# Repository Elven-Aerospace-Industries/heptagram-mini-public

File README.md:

# Heptagram Mini
Open-source simple flight control computer solution

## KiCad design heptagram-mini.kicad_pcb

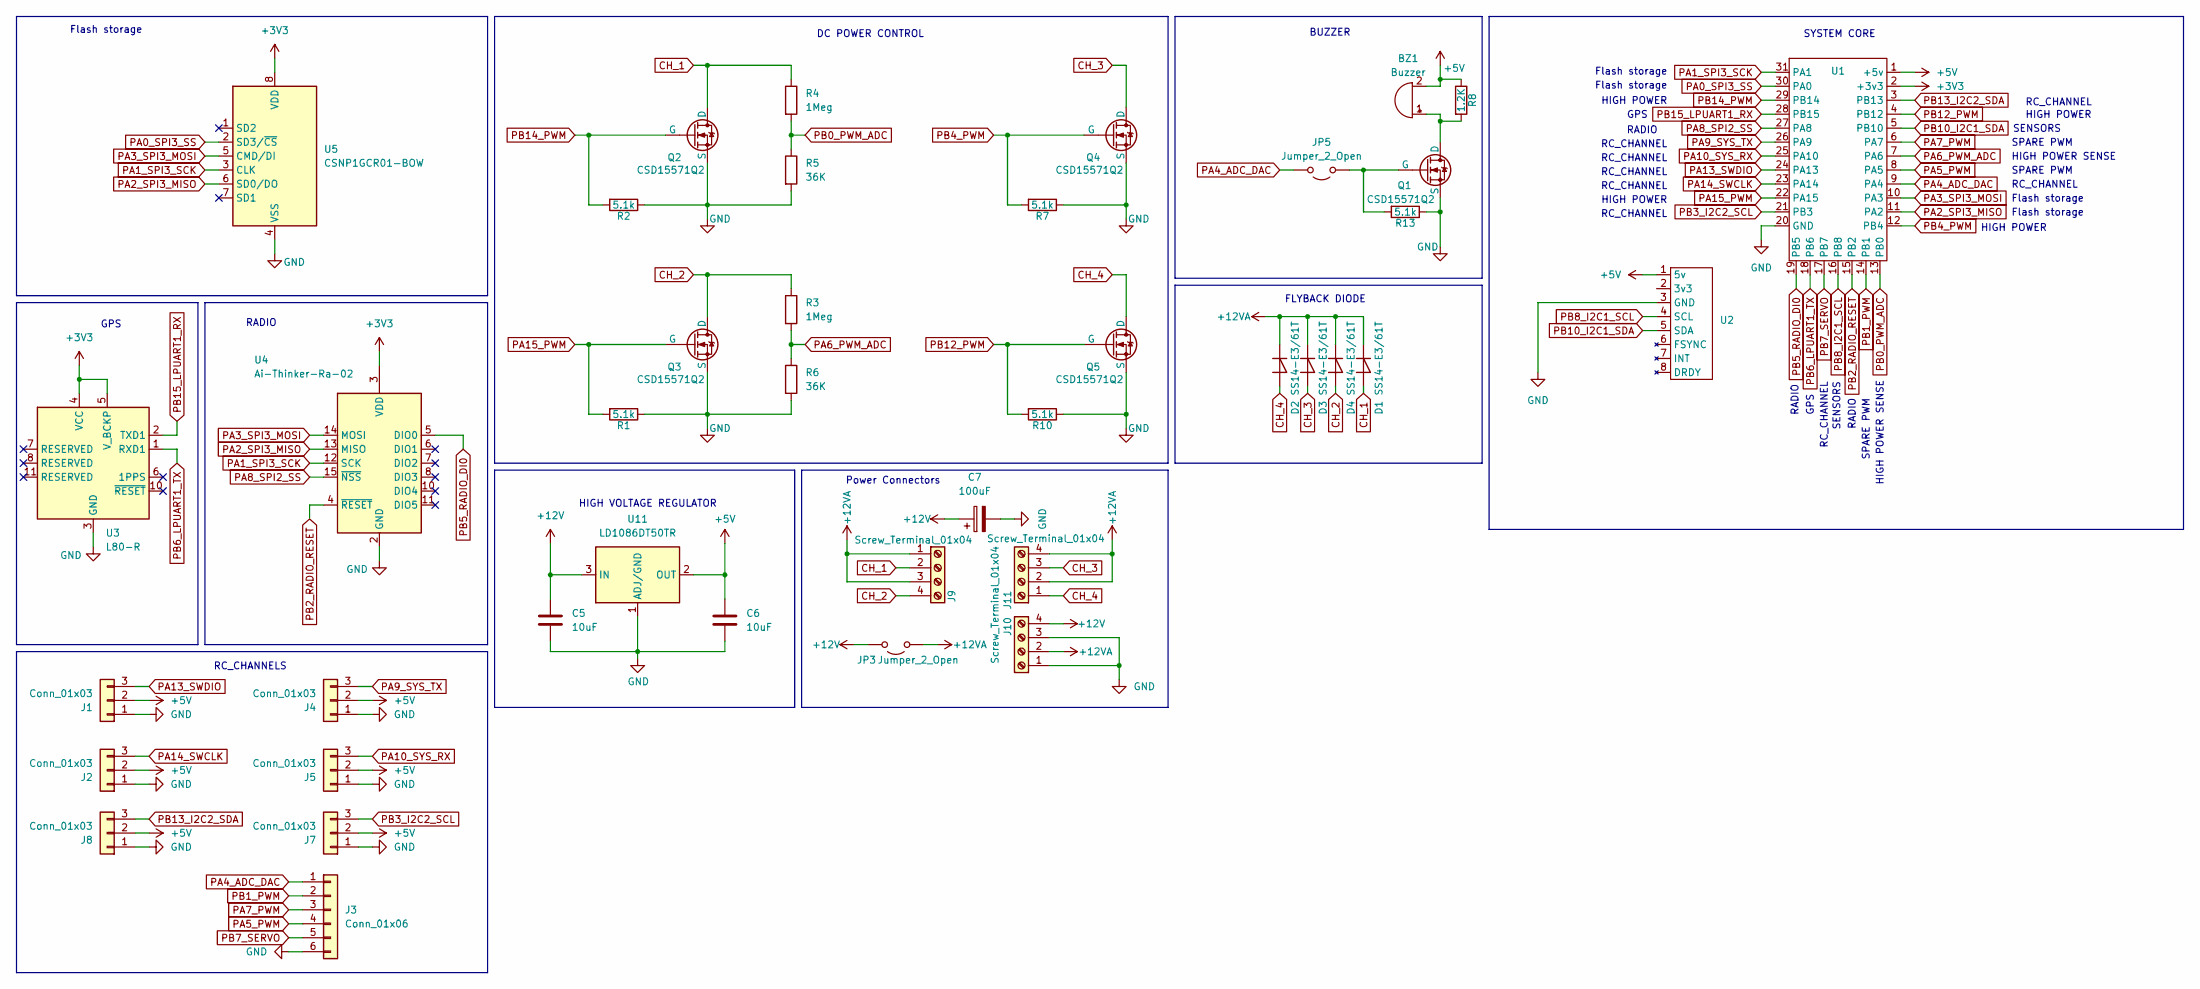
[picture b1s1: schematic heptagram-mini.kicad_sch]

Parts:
BZ1: Buzzer; Buzzer_hand_solder; LCSC C201042
C5, C6: 10uF; C_0402_1005Metric; LCSC C15525
C7: 100uF; CP_EIA-7343-30_AVX-N; LCSC C7223
D1, D2, D3, D4: SS14-E3/61T; D_SMA; LCSC C47460
J1, J2, J4, J5, J7, J8: Conn_01x03; 3pin
J3: Conn_01x06; PinHeader_1x06_P2.54mm_Vertical
J9, J10, J11: Screw_Terminal_01x04; TerminalBlock_Xinya_XY308-2.54-4P_1x04_P2.54mm_Horizontal
JP3, JP5: Jumper_2_Open; SolderJumper-2_P1.3mm_Open_RoundedPad1.0x1.5mm
Q1, Q2, Q3, Q4, Q5: CSD15571Q2; flight_computer_Texas_DQK; LCSC C412825
R1, R2, R7, R10, R13: 5.1k; R_0402_1005Metric_Pad0.72x0.64mm_HandSolder; LCSC C25905
R3, R4: 1Meg; R_0805_2012Metric; LCSC C17514
R5, R6: 36K; R_0805_2012Metric; LCSC C4360
R8: 1.2K; R_0603_1608Metric_Pad0.98x0.95mm_HandSolder; LCSC C22765
U1: laplace0_lite
U2: GY87
U3: L80-R; Quectel_L80-R; LCSC C3029061
U4: Ai-Thinker-Ra-02; Ai-Thinker-Ra-01-LoRa
U5: CSNP1GCR01-BOW; LGA-8_8x6mm_P1.27mm; LCSC C2691593
U11: LD1086DT50TR; TO-252-2; LCSC C164853

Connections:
+3V3: U1.2 (+3v3), U3.4 (VCC), U3.5 (V_BCKP), U4.3 (VDD), U5.8 (VDD)
+5V: BZ1.2 (-), C6.1, J1.2, J2.2, J4.2, J5.2, J7.2, J8.2, R8.1, U1.1 (+5v), U2.1 (5v), U11.2 (OUT)
+12V: C5.1, C7.1, J10.4, JP3.2 (B), U11.3 (IN)
+12VA: D1.1 (K), D2.1 (K), D3.1 (K), D4.1 (K), J9.1, J9.3, J10.2, J11.2, J11.4, JP3.1 (A)
CH_1: D1.2 (A), J9.2, Q2.3 (D), R4.1
CH_2: D4.2 (A), J9.4, Q3.3 (D), R3.1
CH_3: D3.2 (A), J11.3, Q4.3 (D)
CH_4: D2.2 (A), J11.1, Q5.3 (D)
GND: C5.2, C6.2, C7.2, J1.1, J2.1, J3.6, J4.1, J5.1, J7.1, J8.1, J10.1, J10.3, Q1.2 (S), Q2.2 (S), Q3.2 (S), Q4.2 (S), Q5.2 (S), R1.1, R2.1, R5.2, R6.2, R7.1, R10.1, R13.1, U1.20 (GND), U2.3 (GND), U3.3 (GND), U3.12 (GND), U4.1 (GND), U4.2 (GND), U4.9 (GND), U4.16 (GND), U5.4 (VSS), U11.1 (ADJ/GND)
unnamed: BZ1.1 (+), Q1.3 (D), R8.2
unnamed: JP5.1 (A), Q1.1 (G), R13.2
PA0_SPI3_SS: U1.30 (PA0), U5.2 (SD3/~CS)
PA1_SPI3_SCK: U1.31 (PA1), U4.12 (SCK), U5.3 (CLK)
PA2_SPI3_MISO: U1.11 (PA2), U4.13 (MISO), U5.6 (SD0/DO)
PA3_SPI3_MOSI: U1.10 (PA3), U4.14 (MOSI), U5.5 (CMD/DI)
PA4_ADC_DAC: J3.1, JP5.2 (B), U1.9 (PA4)
PA5_PWM: J3.4, U1.8 (PA5)
PA6_PWM_ADC: R3.2, R6.1, U1.7 (PA6)
PA7_PWM: J3.3, U1.6 (PA7)
PA8_SPI2_SS: U1.27 (PA8), U4.15 (~NSS)
PA9_SYS_TX: J4.3, U1.26 (PA9)
PA10_SYS_RX: J5.3, U1.25 (PA10)
PA13_SWDIO: J1.3, U1.24 (PA13)
PA14_SWCLK: J2.3, U1.23 (PA14)
PA15_PWM: Q3.1 (G), R1.2, U1.22 (PA15)
PB0_PWM_ADC: R4.2, R5.1, U1.13 (PB0)
PB1_PWM: J3.2, U1.14 (PB1)
PB2_RADIO_RESET: U1.15 (PB2), U4.4 (~RESET)
PB3_I2C2_SCL: J7.3, U1.21 (PB3)
PB4_PWM: Q4.1 (G), R7.2, U1.12 (PB4)
PB5_RADIO_DI0: U1.19 (PB5), U4.5 (DIO0)
PB6_LPUART1_TX: U1.18 (PB6), U3.1 (RXD1)
PB7_SERVO: J3.5, U1.17 (PB7)
PB8_I2C1_SCL: U1.16 (PB8), U2.4 (SCL)
PB10_I2C1_SDA: U1.5 (PB10), U2.5 (SDA)
PB12_PWM: Q5.1 (G), R10.2, U1.4 (PB12)
PB13_I2C2_SDA: J8.3, U1.3 (PB13)
PB14_PWM: Q2.1 (G), R2.2, U1.29 (PB14)
PB15_LPUART1_RX: U1.28 (PB15), U3.2 (TXD1)

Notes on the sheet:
DC POWER CONTROL
Flash storage
RADIO
RC_CHANNEL
SPARE PWM
HIGH POWER
SYSTEM CORE
GPS
HIGH VOLTAGE REGULATOR
HIGH POWER SENSE
SENSORS
BUZZER
Power Connectors
RC_CHANNELS
FLYBACK DIODE

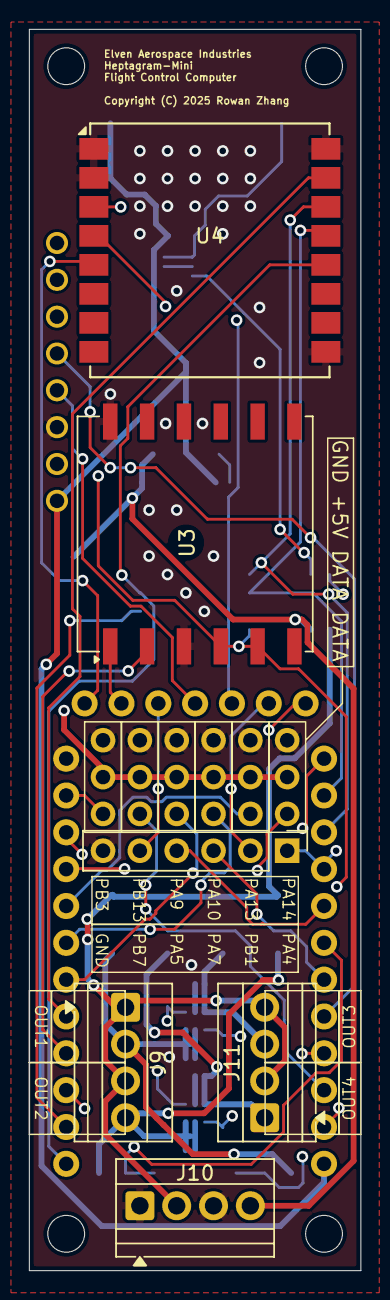
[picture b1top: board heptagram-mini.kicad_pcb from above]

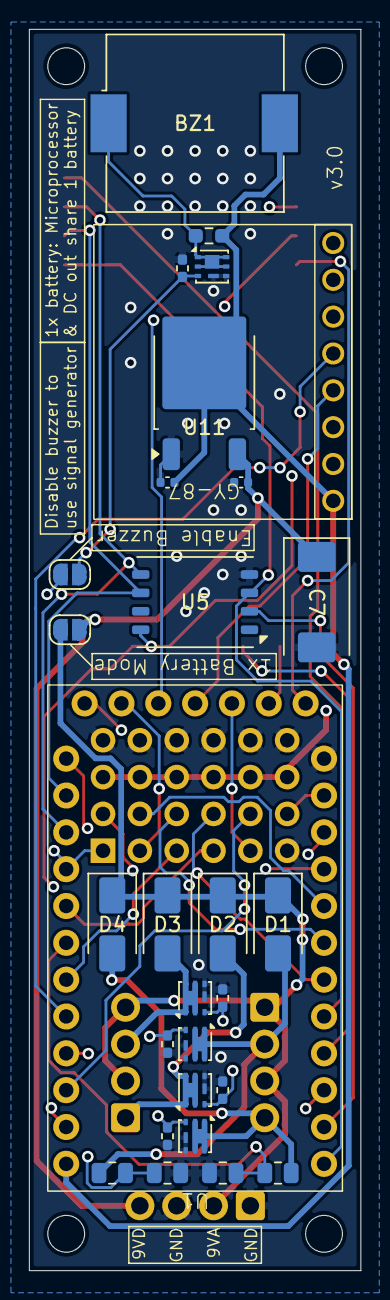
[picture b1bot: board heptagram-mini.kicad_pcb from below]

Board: 4 copper layers, 22.9 x 85.6 mm, 41 parts (29 on the bottom side), 39 nets.

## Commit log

2026-01-12 v3.0
2026-01-12 Added datasheet
2026-03-07 Updated datasheet
2026-05-20 v4.1 The HAM radio update

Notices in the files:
heptagram-mini.kicad_pcb:
Copyright (C) 2025 Rowan Zhang
License URL: https://creativecommons.org/licenses/by-sa/4.0
License: CC BY-SA 4.0
